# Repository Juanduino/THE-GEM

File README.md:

# THE GEM

 State of the art GROW RAYDIATOR [light/heatsource] w. current injection 25-30amp
 
 FEATURES: 
 
 CREE XLAMP LED´s
 
 4 x MAX31725 temperature sensors
 
 4 x 12v PWM FAN (4pin) connectors.
 
 4 x individually controlled strings w. current sensor. (40amp rated mosfets).

 This is a PAR light project based on the high-current controller M4SUBDRV (https://github.com/Juanduino/THE-DIMMER_M4SDRV_V1)
 
 The CREE XLAMP LED´s is one of the most advanced horticultural light emitters on the market. They have a huge µmol/watt output. 
 
 (Source: https://www.cree.com/led-components/media/documents/CreeXLampHorticultureFeatureSheet.pdf)
 
 One controller can inject current into 4 seperate channels of up to 8 amp per channel.  (note: The white LED´s heats up faster compared to red´s and blues.)

 Two controllers (6 lamps) will run of a 12v 500-1000watt PSU (Powersupply). Many have old PSU´s sitting in computers, which typically have a 500watt capasity.
 
 The goal of the project is to make a smart plant grow lamp, which controls the light intensity based on temperature sensor input.
 
 By making the lamp output pwm and temperature controlled, the final capacity of the lamp depends on the amount of cooling applied or the amount of heating allowed.
 
 Because the controller can be connected to a CAN (Controller Area Network) and USB, you can monitor and control each string/color (Red, Blue, White)

 HEAT CIRCULATION
 
Although LED´s have become more efficient than the old gas-type bulbs, when driving the LED´s with high currents, there will be generated heat. How to re-cirkel and use that energy is a major task.

Case: Imagine a part of your living space, where you can grow greens all year round, and at the same time use the heat-output to warm up your space. This could especially benefit families in developing countries, where this type of technology, not only can provide food all year, but also expand the outdoor season by starting sprouts indoor, in a controlled environment, before they are ready to be planted out. 

Another mayer benefit by utilising the radiated heat, is the possibility to fully heat your living space with green energy. This means less foresting for wood to burn. Less Co2 emissions from NOT BURNING WOOD or other carbon-based energy sources. Naturally all this requires a solid environmentally friendly energy infrastructure.

By introducing CAN (Controller Area Network) to the "intelligent" GEM/lamps, and possibly wireless connections, there are many possibilities to make smart solutions for re-circulation of the heat-output.

A larger version, without the possibility or need to connect smaller Gem´s. approx 400w (MAX) 

 Changelog:
 
 My Focus is now the 400watt lamp and to cut down on complexity.
 
 Have decided against the 5th LED channel. The white LED´s will be mounted on a fully white and bright GEM. The GemX4 is still 98 very intens LED´s, so the reeason is also based on a considoration for the final BOM count and the fans current consomption.

White LED´s use energy to lite up the full visible spectrum. The Red and Blue only one wavelentht(area) and  is terefore cooler in use. The difference  between the red and blue wavelength  is another matter. 

Added 4 4pin PWM FAN plug headers. One is for the outtside end-fan, which sits just before the controller and therefore cools the conttroller alswell.

For office invironment the fully white GEM would be more pleasant for the  humaan eye.  In a school schenario the lamps would  be part of  photon to plant  growth process. 

Inside the lamp another 3 eg. 60mm fans can be mounted. This all  depennds on the enclosure design. The fans will be controlled by a common PWM puls.

 To connect a 120mm fan as the front cooller,  you need the adabtor 3D print  file.
 
 As seen in above image, the power cables can be solderen in  by using the  split&twist tech.
 
 To add wireless com. you need a Bluetooth / Wify or NB add-onn module on the I2C or SPI bus.
 
 (Controller: https://github.com/Juanduino/THE-DIMMER_M4SDRV_V1)

Added 4 x MAX31725MTA+T temperature sensor on I2C bus. (up to 150C). (https://datasheets.maximintegrated.com/en/ds/MAX31725.pdf)

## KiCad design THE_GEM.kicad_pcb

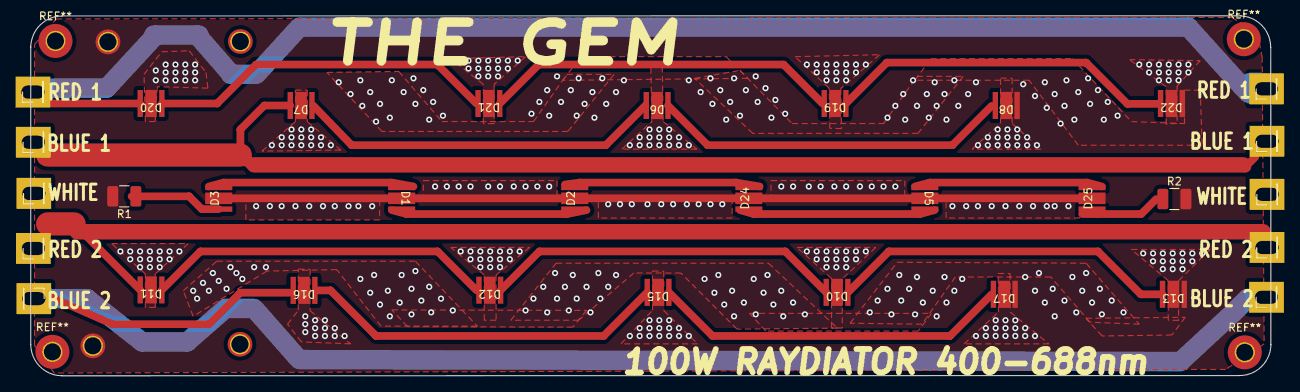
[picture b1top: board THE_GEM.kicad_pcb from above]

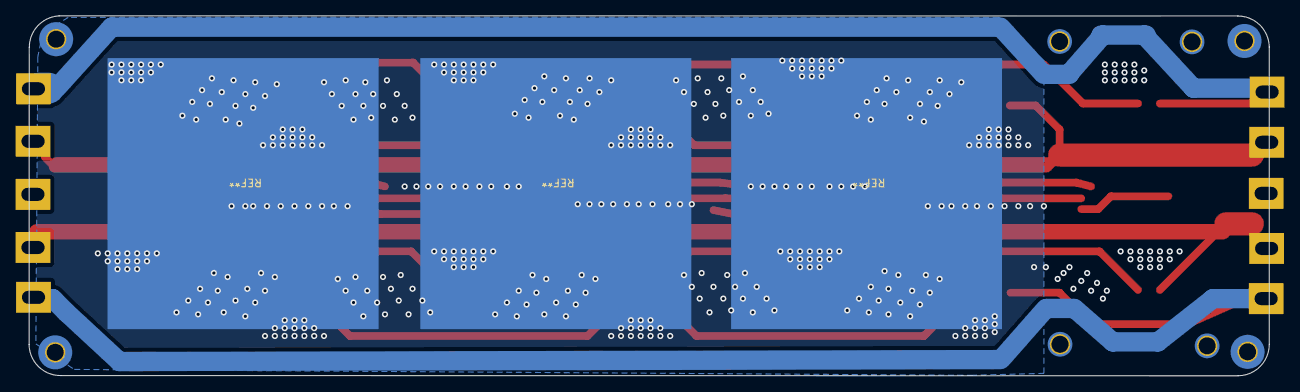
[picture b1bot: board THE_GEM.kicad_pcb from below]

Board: 4 copper layers, 160.2 x 46.5 mm, 36 parts (4 on the bottom side), 22 nets.

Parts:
D1, D2, D3, D5, D6, D7, D8, D10, D11, D12, D13, D15, D16, D17, D19, D20, D21, D22, D24, D25: LED; CREE XPG3
H1, H2, H3, H4: MountingHole_Pad; MountingHole_2.2mm_M2_ISO14580_Pad_TopBottom
J1, J1#2, J5, J5#2, J6, J6#2, J6#3, J6#4, J11, J11#2: Conn_01x01; PinHeader_1x01_P2.54mm_Vertical
R1, R2: 2.7ohm; R_1210_3225Metric_Pad1.42x2.65mm_HandSolder

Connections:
BLUE_PHASE1: D7.2 (A), J1.1, J1#2.1
BLUE_PHASE2: D16.2 (A), J5.1, J5#2.1
GND: D1.3 (GND), D2.3 (GND), D3.3 (GND), D5.3 (GND), D6.3 (GND), D7.3 (GND), D8.1 (K), D8.3 (GND), D10.3 (GND), D11.3 (GND), D12.3 (GND), D13.1 (K), D13.3 (GND), D15.3 (GND), D16.3 (GND), D17.1 (K), D17.3 (GND), D19.3 (GND), D20.3 (GND), D21.3 (GND), D22.1 (K), D22.3 (GND), D24.3 (GND), D25.3 (GND), H3.1, H4.1, R1.2, R2.2
MOS1_OUT: D2.2 (A), D24.2 (A)
unnamed: D1.1 (K), D3.2 (A)
unnamed: D1.2 (A), D2.1 (K)
unnamed: D3.1 (K), R1.1
unnamed: D6.1 (K), D8.2 (A)
unnamed: D6.2 (A), D7.1 (K)
unnamed: D10.1 (K), D13.2 (A)
unnamed: D10.2 (A), D12.1 (K)
unnamed: D11.1 (K), D12.2 (A)
unnamed: D15.1 (K), D17.2 (A)
unnamed: D15.2 (A), D16.1 (K)
unnamed: D19.1 (K), D22.2 (A)
unnamed: D19.2 (A), D21.1 (K)
unnamed: D20.1 (K), D21.2 (A)
unnamed: D5.2 (A), D24.1 (K)
unnamed: D25.1 (K), R2.1
unnamed: D5.1 (K), D25.2 (A)
RED_PHASE1: D11.2 (A), J6.1, J6#2.1, J6#3.1, J6#4.1
RED_PHASE2: D20.2 (A), J11.1, J11#2.1

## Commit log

2020-10-14 In development
2020-10-14 Rearange
2020-12-05 Git commit
2020-12-05 Added perspectve
2020-12-07 upgrade
2020-12-07 Upgrade 4 x MAX31725 temp sensor
